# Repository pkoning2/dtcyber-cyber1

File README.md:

# dtcyber-cyber1 repository
This is a Git conversion of the Subversion repository maintained by Paul Koning at the akdesign.org server.  The purpose of the conversion is to make it easier to access
and for the convenience of those more familiar with Git.  The conversion was run on April 8, 2025.  The Subversion server will be changed to read-only and at some later 
time be taken off-line.

## History
This DtCyber fork was started many years ago before Tom Hunter moved to generally accessible source control and before he switched DtCyber to the GPL license.  
The original license is still on this code; please read it.  It is not a normal open source license; you will see it has some specific restrictions.
I have not considered moving to an open source license (GPL would be the obvious choice) mainly because to do it properly would require the explicit
consent of all the authors of the code here.

This fork fairly closely tracked Tom Hunter's main releases for some time, but not in recent years.  Being more precise would require research.  There are additional
changes and new features made for the benefit of the PLATO system described at http://cyber1.org (the actual system's host is cyberserv.org).

## Read-only access
Read only access is open to all.  Please be aware of the license.  It is *not* a standard open source license.

## Read/write access
As with the Subversion repository, read/write access is by request.  I have not carried over the access list of the Subversion repository; please contact me if you 
would like read/write access.

## Additional content
While not strictly DtCyber components, the repository also contains some other Cyber system related work.  

The `vhdl` subdirectory contains the wirelists of the CDC 6600,
from Bitsavers via OCR, and a gate level VHDL model constructed from these.  That model is currently partly functional (PP and display controller work, the CPU not yet).

The `spice` subdirectory contains an attempt at creating a SPICE model (written for the open source "ngspice" version) of the DD60 display console.  The intent is to
model how it distorts the character plotting waveforms generated by the 6612 controller, resulting in the screen images familiar from old photos.
At the moment the model is mostly written but it does not yet deliver anything close to the actual waveforms it should.

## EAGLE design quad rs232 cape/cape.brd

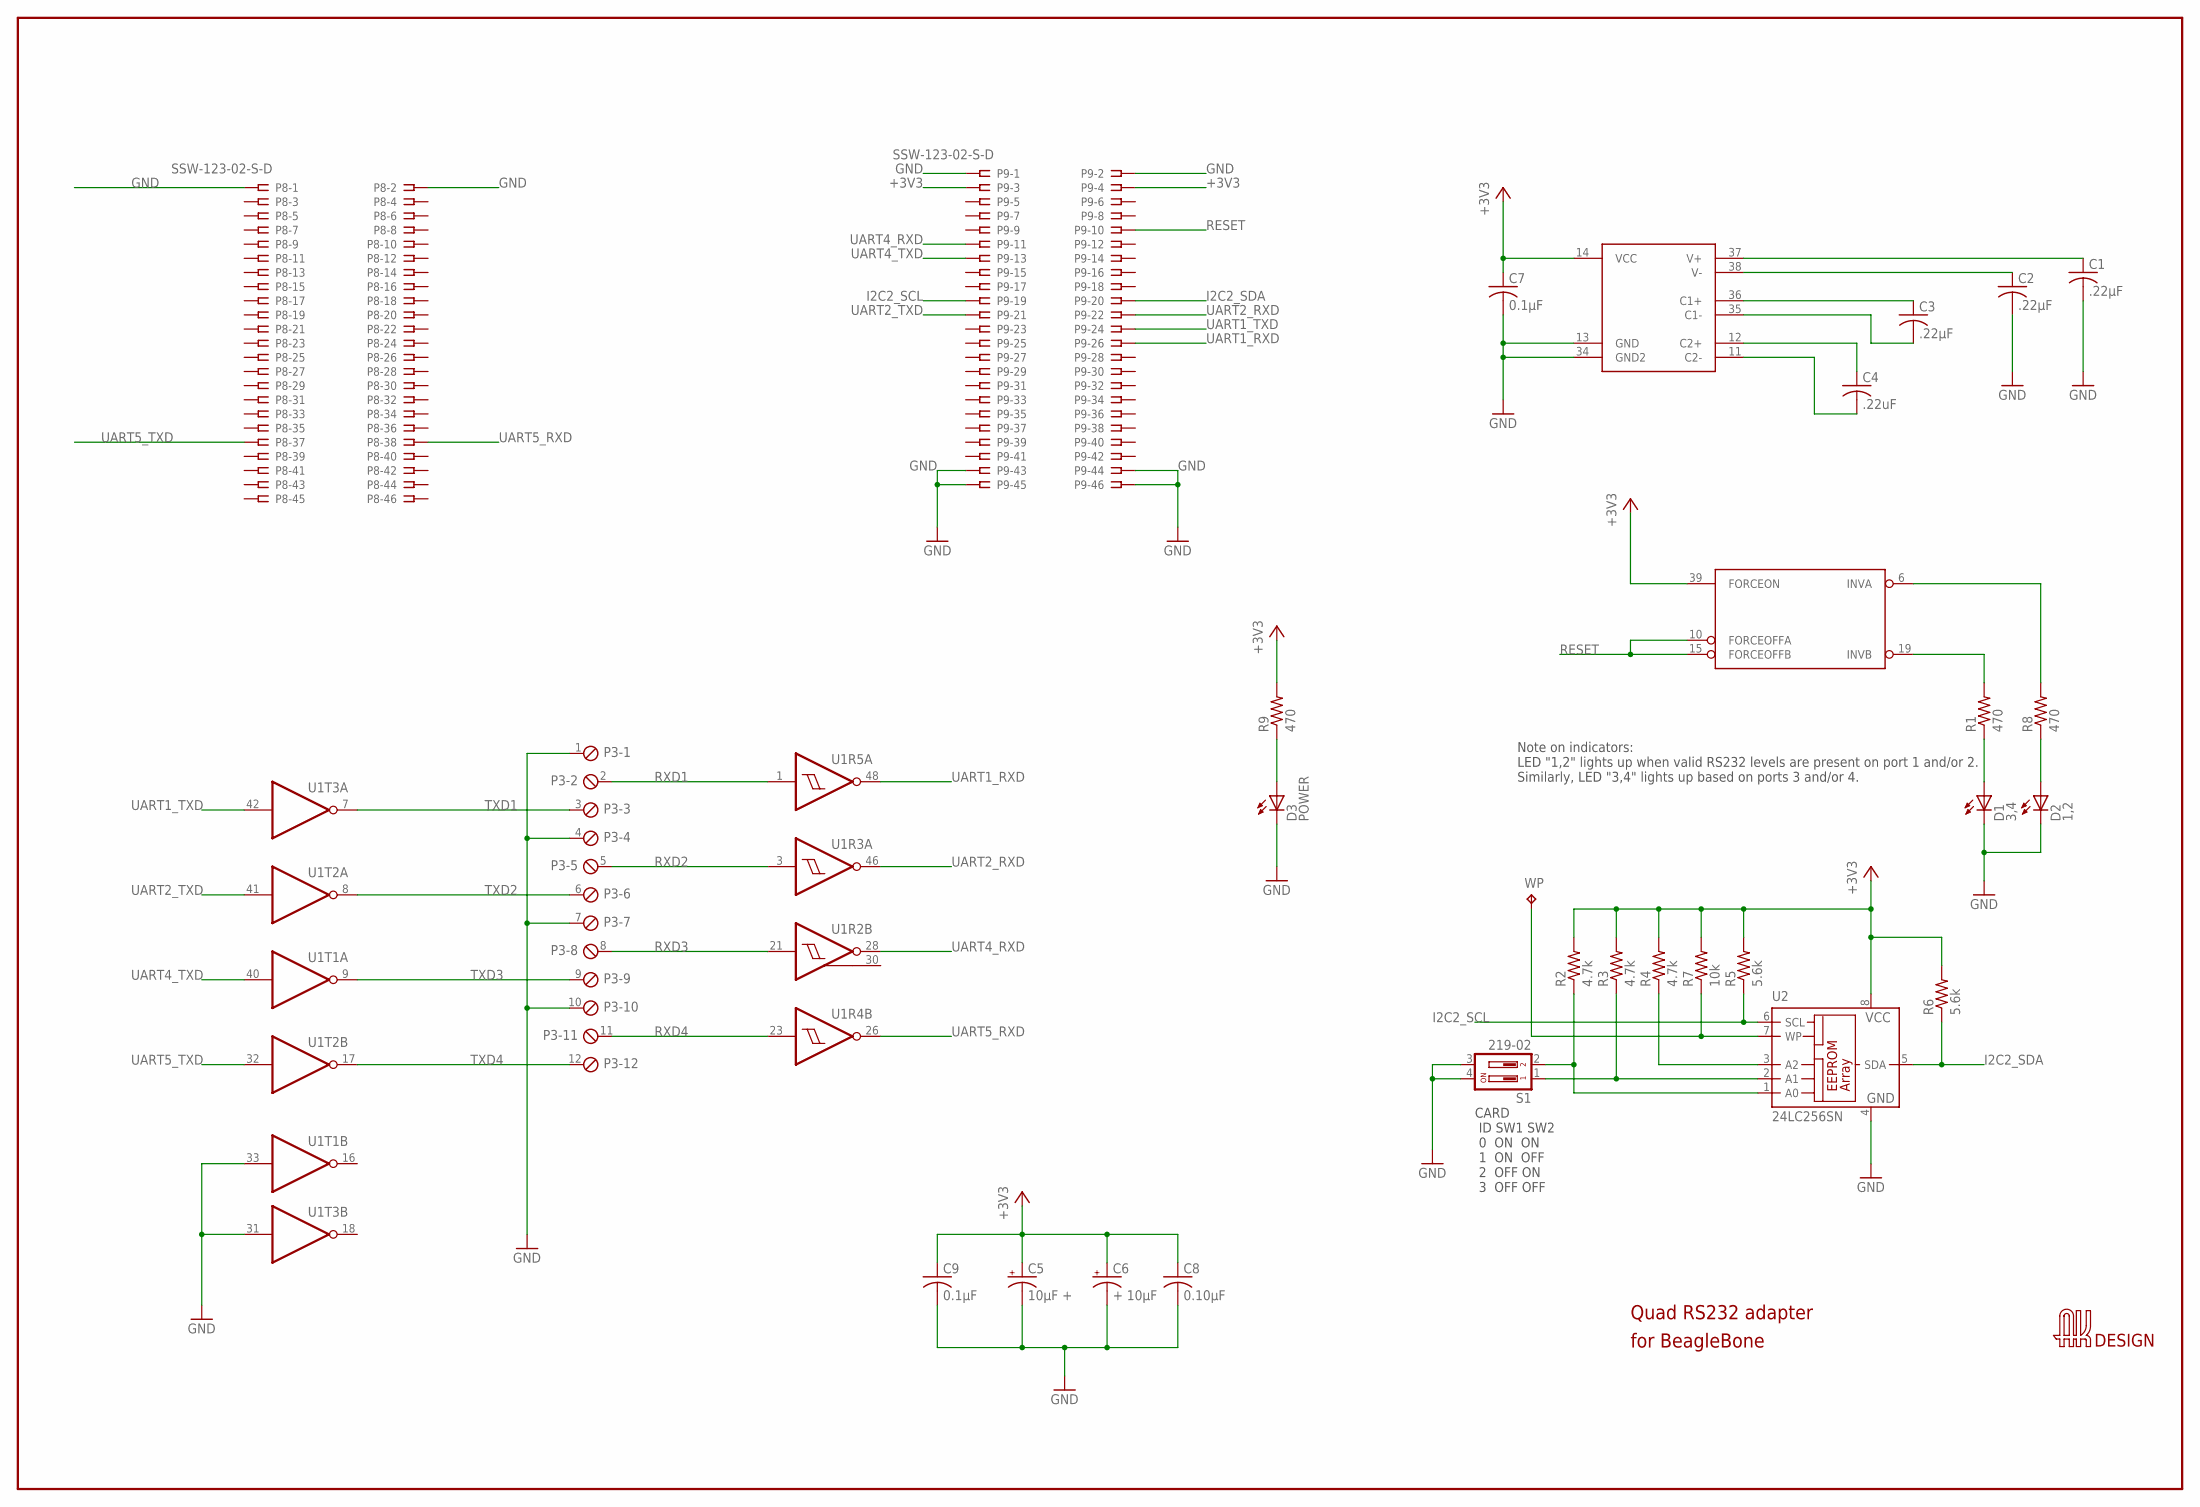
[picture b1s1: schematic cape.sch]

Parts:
C1, C2, C3: .22µF; C0603
C4: .22uF; C0603
C5: 10µF +; C1206
C6: + 10µF; C1206
C7, C9: 0.1µF; C0603
C8: 0.10µF; C0603
D1: 3,4; CHIPLED_0603
D2: 1,2; CHIPLED_0603
D3: POWER; CHIPLED_0603
P3: MPT12; 12POL254
P8, P9: SSW-123-02-S-D
R1, R8, R9: 470; R0603
R2, R3, R4: 4.7k; R0603
R5, R6: 5.6k; R0603
R7: 10k; R0603
S1: 219-02; CTS-219-02
U1: SN75C23243; SSOP48DL
U2: 24LC256SN; SO-08
U$3: LOGO/PLACE; LOGO_PLACE
WP: TPTP15SQ; TP15SQ

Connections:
+3V3: C5.1 (+), C6.1 (+), C7.1, C8.1, C9.1, P9.3, P9.4, R2.2, R3.2, R4.2, R5.2, R6.2, R7.2, R9.2, U1.14 (VCC), U1.39 (FORCEON), U2.8 (VCC)
A0: R2.1, S1.2, U2.1 (A0)
A1: R3.1, S1.1, U2.2 (A1)
A2: R4.1, U2.3 (A2)
C1+: C3.1, U1.36 (C1+)
C1-: C3.2, U1.35 (C1-)
C2+: C4.1, U1.12 (C2+)
C2-: C4.2, U1.11 (C2-)
GND: C1.2, C2.2, C5.2 (-), C6.2 (-), C7.2, C8.2, C9.2, D1.C, D2.C, D3.C, P3.1, P3.4, P3.7, P3.10, P8.1, P8.2, P9.1, P9.2, P9.43, P9.44, P9.45, P9.46, S1.3, S1.4, U1.13 (GND), U1.31 (I), U1.33 (I), U1.34 (GND2), U2.4 (GND)
I2C2_SCL: P9.19, R5.1, U2.6 (SCL)
I2C2_SDA: P9.20, R6.1, U2.5 (SDA)
INVA: R8.2, U1.6 (INVA)
INVB: R1.2, U1.19 (INVB)
LED1_2: D2.A, R8.1
LED3_4: D1.A, R1.1
unnamed: D3.A, R9.1
RESET: P9.10, U1.10 (FORCEOFFA), U1.15 (FORCEOFFB)
RXD1: P3.2, U1.1 (I)
RXD2: P3.5, U1.3 (I)
RXD3: P3.8, U1.21 (I)
RXD4: P3.11, U1.23 (I)
TXD1: P3.3, U1.7 (O)
TXD2: P3.6, U1.8 (O)
TXD3: P3.9, U1.9 (O)
TXD4: P3.12, U1.17 (O)
UART1_RXD: P9.26, U1.48 (O)
UART1_TXD: P9.24, U1.42 (I)
UART2_RXD: P9.22, U1.46 (O)
UART2_TXD: P9.21, U1.41 (I)
UART4_RXD: P9.11, U1.28 (O)
UART4_TXD: P9.13, U1.40 (I)
UART5_RXD: P8.38, U1.26 (O)
UART5_TXD: P8.37, U1.32 (I)
V+: C1.1, U1.37 (V+)
V-: C2.1, U1.38 (V-)
WP: R7.1, U2.7 (WP), WP.TP

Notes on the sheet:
Quad RS232 adapter
for BeagleBone
CARD ID SW1 SW2 0 ON ON 1 ON OFF 2 OFF ON 3 OFF OFF
Note on indicators: LED "1,2" lights up when valid RS232 levels are present on port 1 and/or 2. Similarly, LED "3,4" lights up based on ports 3 and/or 4.

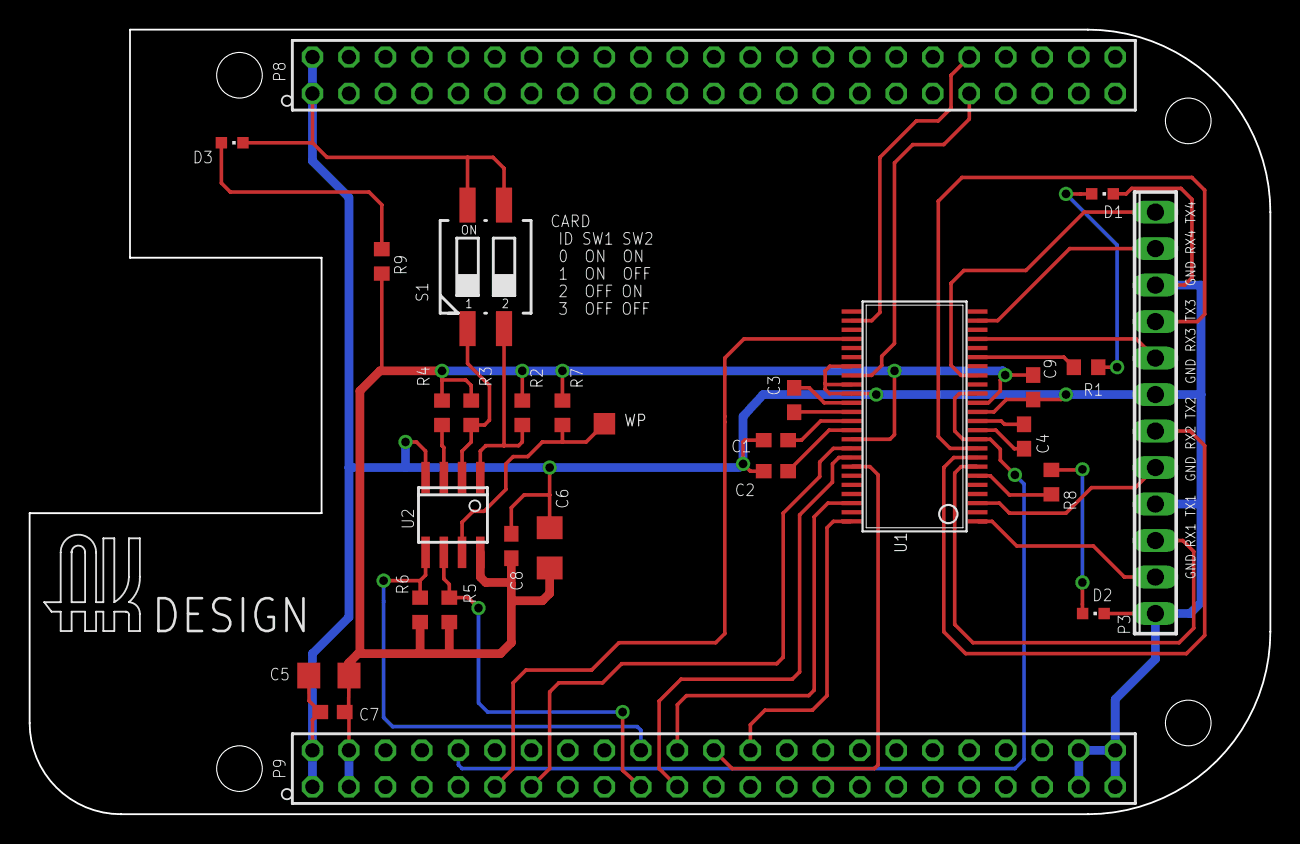
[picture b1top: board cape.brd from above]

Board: 2 copper layers, 86.4 x 54.6 mm, 29 parts (0 on the bottom side), 36 nets.

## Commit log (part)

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2017-05-10 Some edits through row B
2017-05-12 Another typo
2017-05-12 Fixes through page 172
2017-05-12 Module for chassis 8
2017-05-16 First pass done
2017-05-18 Clean up wire lengths
2017-05-19 Fix missing pins
2017-05-19 Small output formatting fix
2017-05-20 Fix arch names
2017-05-22 Final batch of module definitions for chassis 8
2017-05-22 Fix cabling for exchange resume to Ch 1.
2017-05-23 Change readmodule calling convention
2017-05-24 More fixes, wlist.py accepts it now
2017-05-24 Corrections for chassis 6
2017-05-24 Allow wires that are used at coax pins
2017-05-24 Back to the earlier wire list
2017-05-28 Wide display option
2017-06-05 Remove unused element
2017-06-05 Remove another mod that wasn't a good idea
2017-06-06 Some more annotations
2017-06-13 Some more and moved traces
2017-06-15 Reference higher SN pages
2017-06-16 Change the four system clock signals to 'sysclk1' etc.
2017-06-18 Fix clock phasing to correct issue problem
2017-06-21 More scoreboard signals
2017-06-21 Add branch unit
2017-06-22 Fix timing issue in R register load
2017-06-23 Add L control
2017-06-26 Log memory writes during test runs
2017-07-14 Change the wire lists to contain what was in the originals.
    Any changes needed are now in "correction files" which wlist.py knows
    how to process. The naming convention is that chassis<n>.corr files
    fix errors in the original (missing wires, mismatches between
    endpoints where the correct answer is clear, etc.).
    chassis<n>model.corr files are changes made to make things work in the
    VHDL modeling environment (and, eventually, in the VHDL synthesis).
2017-07-17 Handle aliasing of coax signals
2017-07-18 Comments
2017-07-18 Fix timing around instruction go control
2017-07-20 Add support for wire 'length' in ns. Fix U1->K and K->R so branches now go to the right spot
2017-07-20 Fix missing signal sources
2017-07-20 Add some branch stack signals
2017-07-21 Fix timing to make in-stack branches work
2017-07-21 Can now execute (once) a loop in the stack
2017-07-28 Fix scan error
2017-07-28 Comments cleanup
2017-10-05 Add some additional documentation
2017-11-07 Suppress annoying LLVM warning
2017-11-16 Small tweaks for NOS 1.4 tests, CYBIS release tests
2017-11-16 Windows bugfixes, fixes to make it build with wx 3.1
2017-12-01 Small fixes to make it build on Mac
2017-12-01 Untabify
2017-12-04 Dale Sinder's latest updates for microtutor and floppy support
2017-12-06 Fix label
2017-12-07 Found another place the initial SP needed to be updated
2017-12-07 Update the Makefile for the new Z80 emulation. Choose which is used (8080 or Z80) as a build setting. Default is Z80; to get 8080, invoke the build as: make USEZ80="" Only the microprocessor emulatio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
    Note that the MSVC build files need to be updated, and in particular
    need to pass in -DUSEZ80 if a Z80 build is needed; the #define is no
    longer in pterm_wx.cpp.
2017-12-07 Added a cast to stop compiler warning.
2017-12-08 Patch two bugs found by Tom Hunter
2017-12-09 Correct floppy changes, Unix case
2017-12-10 Add Reset to File menu when booted from floppy. Add RadioBox to choose level of mtutor to run on-line. Have mtutor give up thread for 1 msec on call to r.input if booted from floppy.
2017-12-10 Changes to enable booting level 4 disks.
2017-12-10 Fix typo, fix MS specific data type
2017-12-11 Patch level 2 bug in mtutor and add z80 debugger code.
2017-12-11 Make Z80 verbose check_pcZ80 related stuff a macro.
2017-12-11 Remove 8080 license text since it's not used any longer.
2017-12-11 Remove all 8080 related things and rename variables and functions as appropriate.
2017-12-11 Added void PtermConnDialog::CreateDefaultProfiles. But it's empty now.
2017-12-12 Add default profile creation for current directory.
2017-12-12 Remove redundant code.
2017-12-12 Tweaks to MS build file, may need more work
2017-12-14 Remove redundant include it let creep in.
2017-12-15 Initial commit of pterm source reorganization. This splits the original very large pterm_wx.cpp into a set of files, for the most part one per class. The exception is FrameCanvas, which has both the 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
    This work done largely by Dale Sinder, with Makefile updates and some
    build fixes by Paul Koning.
2017-12-18 Remove ptermx.h
2017-12-18 Change #include guard labels.
2017-12-20 Check for null pointer in dtReado. Had random exceptions on exit. Save, clear and restore mtutor key routing flag in r.xmit.
2017-12-21 Use wxControl rather than wxNotebook for mtutor settings dialog
2017-12-21 Add microtutor settings to makefile
2017-12-22 Include Profile Name in Titlebar when editing a profile. Disable mtutor level selction when boot from disk is selected.
2017-12-22 Remove references to mtutor level user configuration
2017-12-22 Bugfix -- thanks to Tom Hunter for this
2017-12-22 Adjust Makefile, remove obsolete files
2017-12-22 Fix floppy I/O error when opening help window when local window is active
2017-12-22 Fixed this bug report:
    Boot from floppy. Enter shift-stop to terminate the program. (Result is a blank window.) Enter any key ... *crash*. The blank window with the status bar still saying "booted from floppy" is a bit dis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
2017-12-22 First commit of Mtutor Users Guide.
2017-12-22 Add patches for experimental mtutor level (6). 4, 5, and 6 seem to be identical.
2017-12-25 Implement -color display- for level 4 with interpreter patch and new entry points in r. routines.
2017-12-25 Patch interpreter to implement paint (no tag) - flood fill. mtutor only supports solid color paint.
2017-12-25 Remove dead code.
2017-12-26 Refactor bulky patching out of Z80Emulate
2017-12-27 Refactor color patching
2018-01-01 Add a helper method to make z80 debugging better
2018-01-23 Changes from Steve Zoppi dealing with compiler warnings about unreferenced vars/params and type mismatches.
2018-01-24 Add dtnetsubs.h which is a subset of proto.h for pterm.h from Steve Zoppi. Remove proto.h from project. Also more warning suppressions.
2018-01-24 Deal with unused parameter warnings by using unnamed parameters.
2018-02-05 Starting reverse engineering, done timing chain (2 pages)
2018-02-07 Fix bug in disk formatting
2018-02-07 Fix case on Z80emu.h include
2018-02-07 Missed this file
2018-02-12 Fix occasional connection failure at startup in Windows build
2018-02-13 Fix compile warning, delete some obsolete files
2018-02-13 Small layout tweak
2018-02-14 Fix session settings not carrying over to next time it is used; fix trace file parsing
2018-02-16 Attempt to isolate floppy init errors to callers of WriteRAMW or WriteRAM.
2018-02-16 Suppress output message for seek to negative (large positive) locations.
2018-02-20 Add method ReadReset and WriteReset to be used in conjunction with less then a full sector read/write with ReadByte and WriteByte. Possible use with setting PtermHelp context sensitive index.
2018-02-22 Undo some incomplete work that in fact will not be needed.
2018-02-24 Refine Access key help.
2018-02-25 Add local Tab Help skeleton and MTUTOR Help draft 1.
2018-03-09 create ptermhelp.h floppy header from ptermhelp.mte floppy image
2018-03-12 Permit only one help window and allow reuse of it. Remove inappropriate menu items from help window.
2018-03-12 Fix check for program exit
2018-03-13 Change the packaging of the Micrototur floppy image for Pterm help. For Mac and Windows, where there is an easy way to package resource files alongside the executable program, we carry the actual flo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
    The master for the help is now the floppy image file ptermhelp.mte;
    the Linux .h file is generated at build time from that. Having the
    floppy image as part of the program makes it easier to test updates to
    that code: all that is needed is to update that file in the executable
    directory (reso
2018-03-14 Fix build error for dd60
2018-03-15 Set version to 6.0
2018-03-21 Move Accelerator preference to title tab. Remove it for the MAC.
2018-03-22 Make the PtermPrefDialog modeless.
2018-03-22 Allow one Session Settings dialog and one Profile Editor dialog per app instance. Also handle update of profile list in connect dialog for Save As and Delete cases. Note - Missed with previous commit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
2018-03-23 Comment out code related to unimplemented paste options. Will remove later when well into beta.
2018-03-24 Make trim spaces from end of copied text a profile/session settings option with true the default.
2018-03-25 Fix wrong version, bug in ptermversion.py...
2018-03-26 Update to use new pterm dialogs and .mte rather than mtu.
2018-03-27 When loading a profile, if m_scale is 0, set it to 1.
2018-03-28 Bugfix: make character loading work. Cause was that we were sending terminal type zero (Magnavox) which makes the characters go to the wrong memory locations.
2018-03-28 Update help to include just added Zoom, Show Menu, and Show Status bar.
2018-03-28 Code clean up.
2018-03-28 Precalc some values that are used twice.
2018-03-28 Updated help with BILINEAR scaling and radiobox zoom selection.
2018-03-30 Fix Mac build error
2018-04-01 Visual Experiment: Put Headings, Directions, and Notations in Bold Font.
2018-04-03 Fix source tarball contents
2018-04-04 Widen Session Settings Dialog so Display tab does not scroll.
2018-04-04 Comment out unused PtermHelpConnection which is no longer used with Mtutor help.
2018-04-04 Add recent packs
2018-04-04 Keep starting window location with profile rather than global with app.
2018-04-04 second test system
2018-04-05 Remove call to m_canvas->Refresh(false) from r.exec and add to all other r. entry points that write to the screen. Was causing excessive updating of screen OnIdle with resultant blinking of selected 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
2018-04-06 Most recent Help with changed colors and a few typo fixes.
2018-04-07 ForceValidStartPoint to put starting location of window in a safe spot. Also added arbitrary millisecond delay for ppt programmers and mtutor ccode.
2018-04-07 For a multiple display system, make help window appear on same physical display as Top Window rather than main display.
2018-04-07 Change initial m_restoreX/m_retoreY from 0/0 to 50/50.
2018-04-07 Final location sanity check.
2018-04-08 Update help with view menu phrasing.
2018-04-08 Betal 6.0.2 was released, next will be 6.0.3
2018-04-09 SetColors on return from Session Settings only if in Classic mode or if No Color option is selected.
2018-04-10 Put | between status bar middle section entries
2018-04-12 Refactor checking of profile state.
2018-04-12 Fix compile warning
2018-04-13 Remove unneeded Canvas.Refresh()
2018-04-13 Make applications build dual 32/64 on Intel Mac dev systems
2018-04-14 from previous checkin
2018-04-17 Use enum rather than bool for SaveRestoreColors
2018-05-01 Fix for non-SSE builds
2018-05-02 Some performance optimizations to make console slightly less of a CPU hog.
2018-05-02 Clean up connections that are closed. Add support for the CHM site port numbers (5050 and 8050).
2018-10-02 Use MSVC compatible keyword
2020-10-19 Update for newer pyserial
2020-12-01 Add PIDFILE
2021-01-05 Suppress some warnings
2021-01-05 Missing comment
2021-01-27 Mark explicitly python 3
2021-02-23 work in progress: Python version of the 'pf' utility
2022-05-21 Add write, dumpsec
2022-05-25 NOS pack support
2022-05-25 Some cleanups
2022-05-30 V6.0.5:
    NOTE: The Mac release of this version is the last one to support Mac
    OS versions earlier than 10.10, and the last to include PowerPC
    support. Linux binary kits are no longer supplied; Linux users
    should build Pterm from the source tar archive.
    Bugfixes.
    Moved "Enable control characters" profile setting to the Emulation
2022-05-31 Fix pterm link, courtesy William Schaub
2022-09-26 Add error checking to backup file remote copy
2023-02-12 Change sample rate to 44.1kHz
2025-04-08 Add xtext and a batch build deck at the top
2025-04-08 Pterm version 6.0.6
    Small fixes to build procedure.
    Update copyrights.
    Bugfix in copy text when erasing text.
